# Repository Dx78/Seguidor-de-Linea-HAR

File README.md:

"# Seguidor-de-Linea-HAR" 
# Seguidor-de-Linea-HAR

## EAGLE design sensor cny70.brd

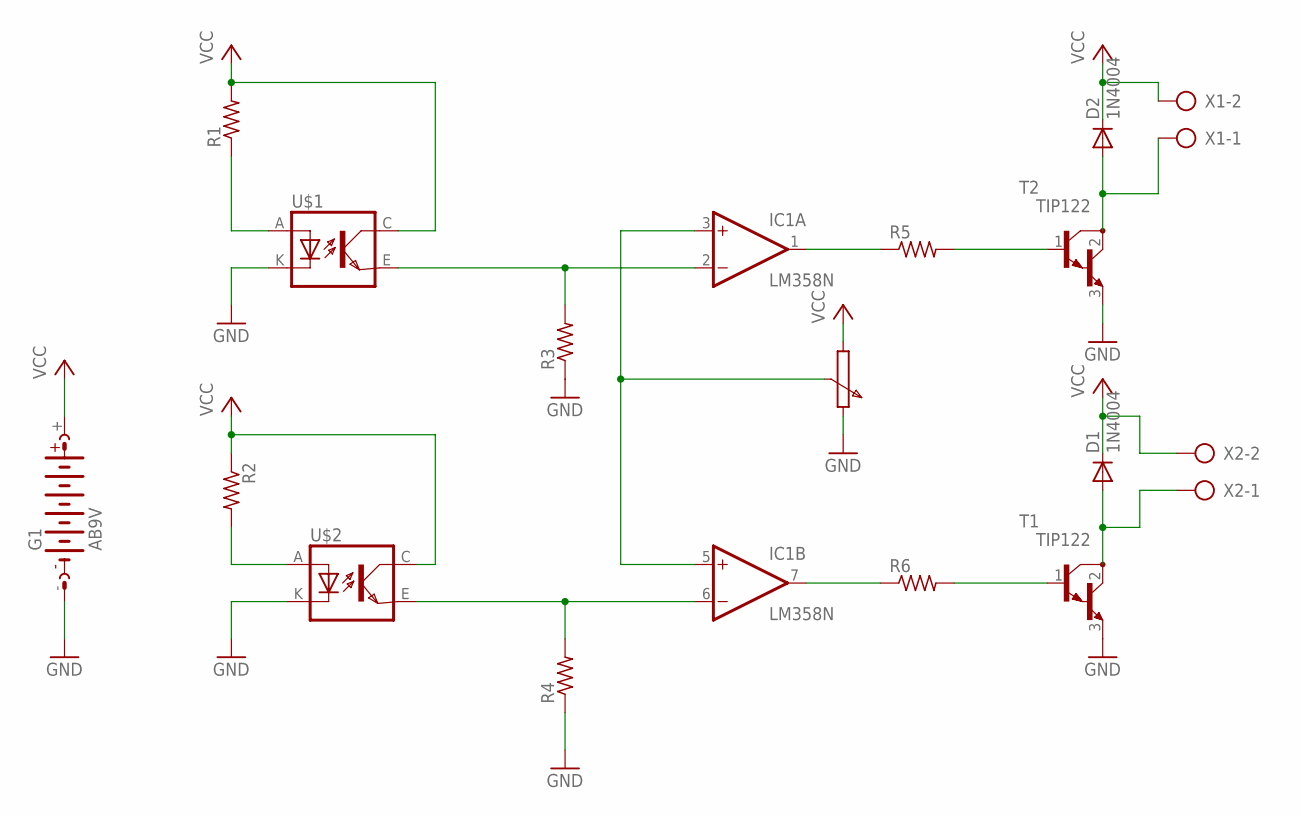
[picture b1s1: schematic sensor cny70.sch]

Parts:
D1, D2: 1N4004; DO41-10
G1: AB9V
IC1: LM358N; DIL08
R1, R2, R3, R4, R5, R6: R-US_0207/10; 0207/10
T1, T2: TIP122; TO220
U$1, U$2: CNY70; 4
X1, X2: AK500/2

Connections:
GND: G1.-, R3.1, R4.1, T1.3 (E), T2.3 (E), U$1.K (C), U$2.K (C)
unnamed: IC1.2 (-IN), R3.2, U$1.E (EMI)
unnamed: IC1.3 (+IN), IC1.5 (+IN)
unnamed: IC1.1 (OUT), R5.1
unnamed: IC1.7 (OUT), R6.1
unnamed: R6.2, T1.1 (B)
unnamed: R5.2, T2.1 (B)
unnamed: D1.A, T1.2 (C), X2.1
unnamed: D2.A, T2.2 (C), X1.1
unnamed: IC1.6 (-IN), R4.2, U$2.E (EMI)
unnamed: R1.1, U$1.A
unnamed: R2.2, U$2.A
V+: IC1.8 (V+)
V-: IC1.4 (V-)
VCC: D1.C, D2.C, G1.+, R1.2, R2.1, U$1.C (COL), U$2.C (COL), X1.2, X2.2

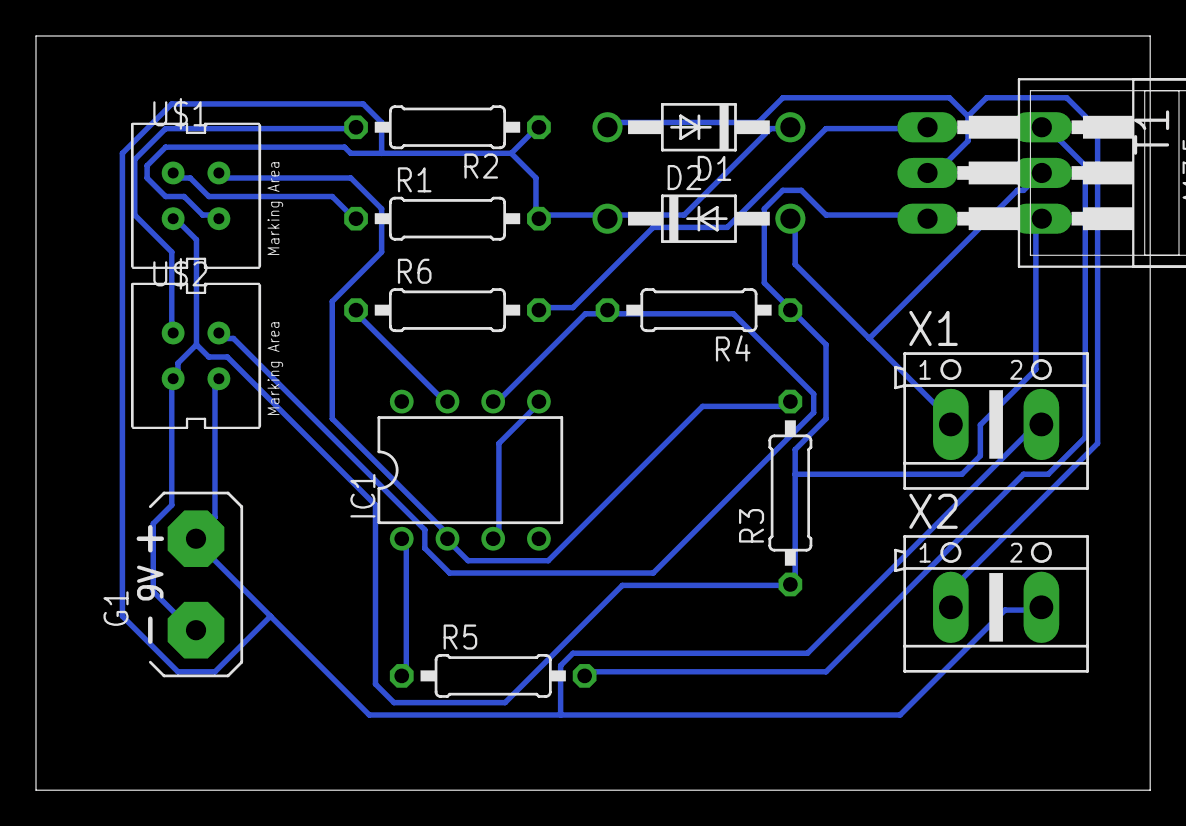
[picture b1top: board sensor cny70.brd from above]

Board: 2 copper layers, 61.9 x 41.9 mm, 16 parts (0 on the bottom side), 13 nets.

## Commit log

2018-06-01 Add files via upload
    Este Es el Diseño de nuestro Robot Seguidor de Lineas
2018-06-03 Add files via upload
    Driver 222222
2018-06-03 Add files via upload
    Programacion Del Robot Seguidor de Lineas
2018-06-13 PROGRAMACION
    Seguidor de linea
